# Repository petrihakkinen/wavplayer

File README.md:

# wav-player
Plays a wav file from SD card using a microcontroller

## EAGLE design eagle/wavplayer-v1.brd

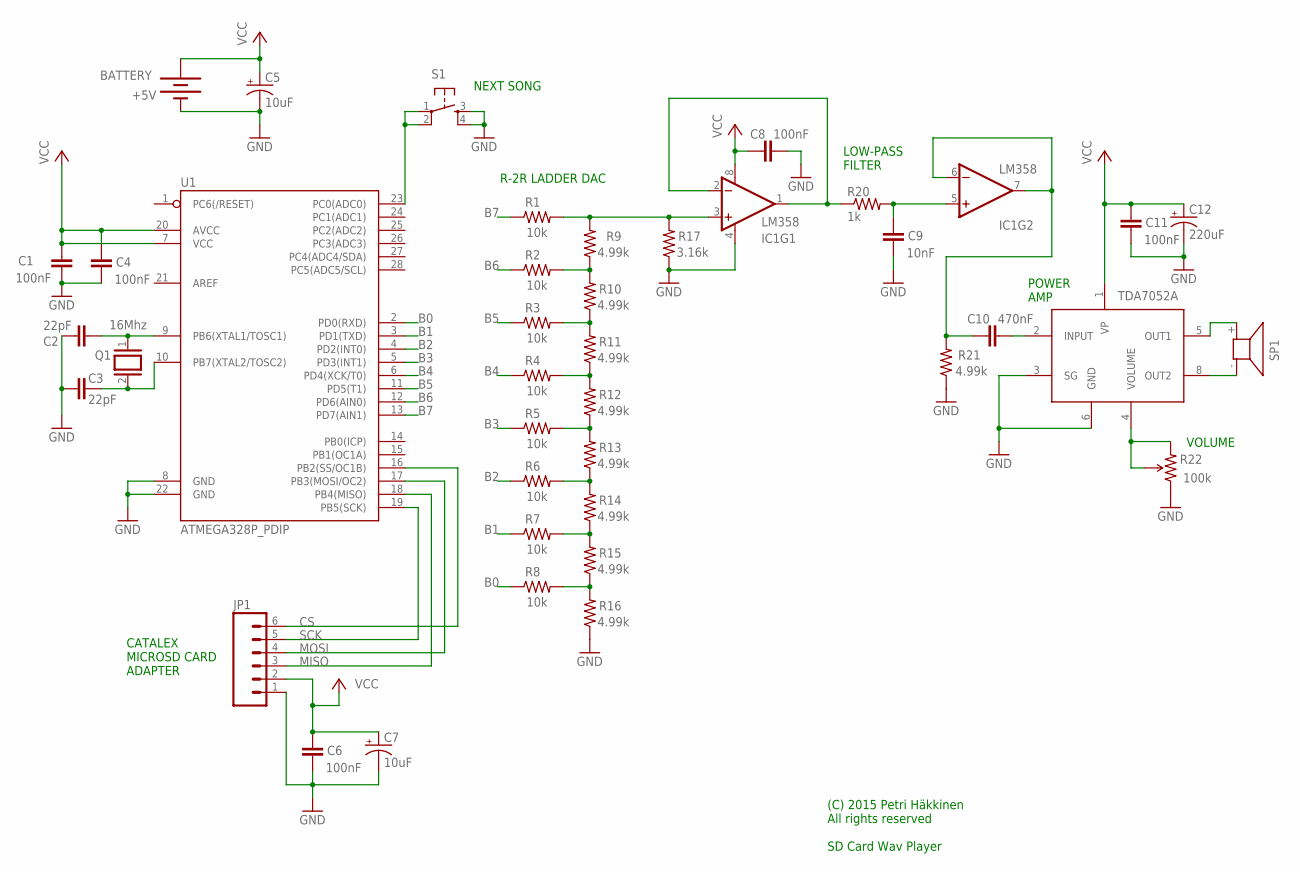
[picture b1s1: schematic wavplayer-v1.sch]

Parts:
BATTERY: +5V; BATTERY-AA
C1, C4, C6, C8, C11: 100nF; CAP-PTH-SMALL
C2, C3: 22pF; CAP-PTH-SMALL
C5, C7: 10uF; CPOL-RADIAL-100UF-25V
C9: 10nF; CAP-PTH-SMALL
C10: 470nF; CAP-PTH-SMALL
C12: 220uF; CPOL-RADIAL-100UF-25V
IC1: LM358; DIP08
JP1: M06LONGPADS; 1X06_LONGPADS
Q1: 16Mhz; QS
R1, R2, R3, R4, R5, R6, R7, R8: 10k; AXIAL-0.4
R9, R10, R11, R12, R13, R14, R15, R16, R21: 4.99k; AXIAL-0.4
R17: 3.16k; AXIAL-0.4
R20: 1k; AXIAL-0.4
R22: 100k; TRIM_POT_PTH
S1: TAC_SWITCHPTH; TACTILE-PTH
SP1: AL11P
U1: ATMEGA328P_PDIP; DIL28-3
U$1: TDA7052B; DIL08

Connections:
B0: R8.P$1 (1), U1.2 (PD0(RXD))
B1: R7.P$1 (1), U1.3 (PD1(TXD))
B2: R6.P$1 (1), U1.4 (PD2(INT0))
B3: R5.P$1 (1), U1.5 (PD3(INT1))
B4: R4.P$1 (1), U1.6 (PD4(XCK/T0))
B5: R3.P$1 (1), U1.11 (PD5(T1))
B6: R2.P$1 (1), U1.12 (PD6(AIN0))
B7: R1.P$1 (1), U1.13 (PD7(AIN1))
CS: JP1.6, U1.16 (PB2(SS/OC1B))
GND: BATTERY.GND@1 (-), C1.2, C2.2, C3.2, C4.2, C5.2 (-), C6.2, C7.2 (-), C8.2, C9.2, C11.2, C12.2 (-), IC1.4 (V-), JP1.1, R16.P$1 (1), R17.P$1 (1), R21.P$1 (1), R22.1 (CCW), S1.3, S1.4, U1.8 (GND), U1.22 (GND), U$1.3 (SG), U$1.6 (GND)
MISO: JP1.3, U1.18 (PB4(MISO))
MOSI: JP1.4, U1.17 (PB3(MOSI/OC2))
unnamed: C2.1, Q1.1, U1.9 (PB6(XTAL1/TOSC1))
unnamed: C3.1, Q1.2, U1.10 (PB7(XTAL2/TOSC2))
unnamed: R4.P$2 (2), R11.P$1 (1), R12.P$2 (2)
unnamed: R5.P$2 (2), R12.P$1 (1), R13.P$2 (2)
unnamed: R6.P$2 (2), R13.P$1 (1), R14.P$2 (2)
unnamed: R3.P$2 (2), R10.P$1 (1), R11.P$2 (2)
unnamed: R7.P$2 (2), R14.P$1 (1), R15.P$2 (2)
unnamed: R2.P$2 (2), R9.P$1 (1), R10.P$2 (2)
unnamed: R8.P$2 (2), R15.P$1 (1), R16.P$2 (2)
unnamed: IC1.3 (+IN), R1.P$2 (2), R9.P$2 (2), R17.P$2 (2)
unnamed: C9.1, IC1.5 (+IN), R20.P$2 (2)
unnamed: C10.1, IC1.6 (-IN), IC1.7 (OUT), R21.P$2 (2)
unnamed: IC1.1 (OUT), IC1.2 (-IN), R20.P$1 (1)
unnamed: SP1.- (1), U$1.8 (OUT2)
unnamed: C8.1, IC1.8 (V+)
unnamed: SP1.+ (2), U$1.5 (OUT1)
unnamed: C10.2, U$1.2 (INPUT)
unnamed: R22.2 (WIPER), R22.3 (CW), U$1.4 (VOLUME)
unnamed: S1.1, S1.2, U1.23 (PC0(ADC0))
SCK: JP1.5, U1.19 (PB5(SCK))
VCC: BATTERY.PWR@1 (+), C1.1, C4.1, C5.1 (+), C6.1, C7.1 (+), C11.1, C12.1 (+), JP1.2, U1.7 (VCC), U1.20 (AVCC), U$1.1 (VP)

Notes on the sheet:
(C) 2015 Petri Häkkinen All rights reserved SD Card Wav Player
VOLUME
TDA7052A
LOW-PASS FILTER
R-2R LADDER DAC
CATALEX MICROSD CARD ADAPTER
POWER AMP
NEXT SONG

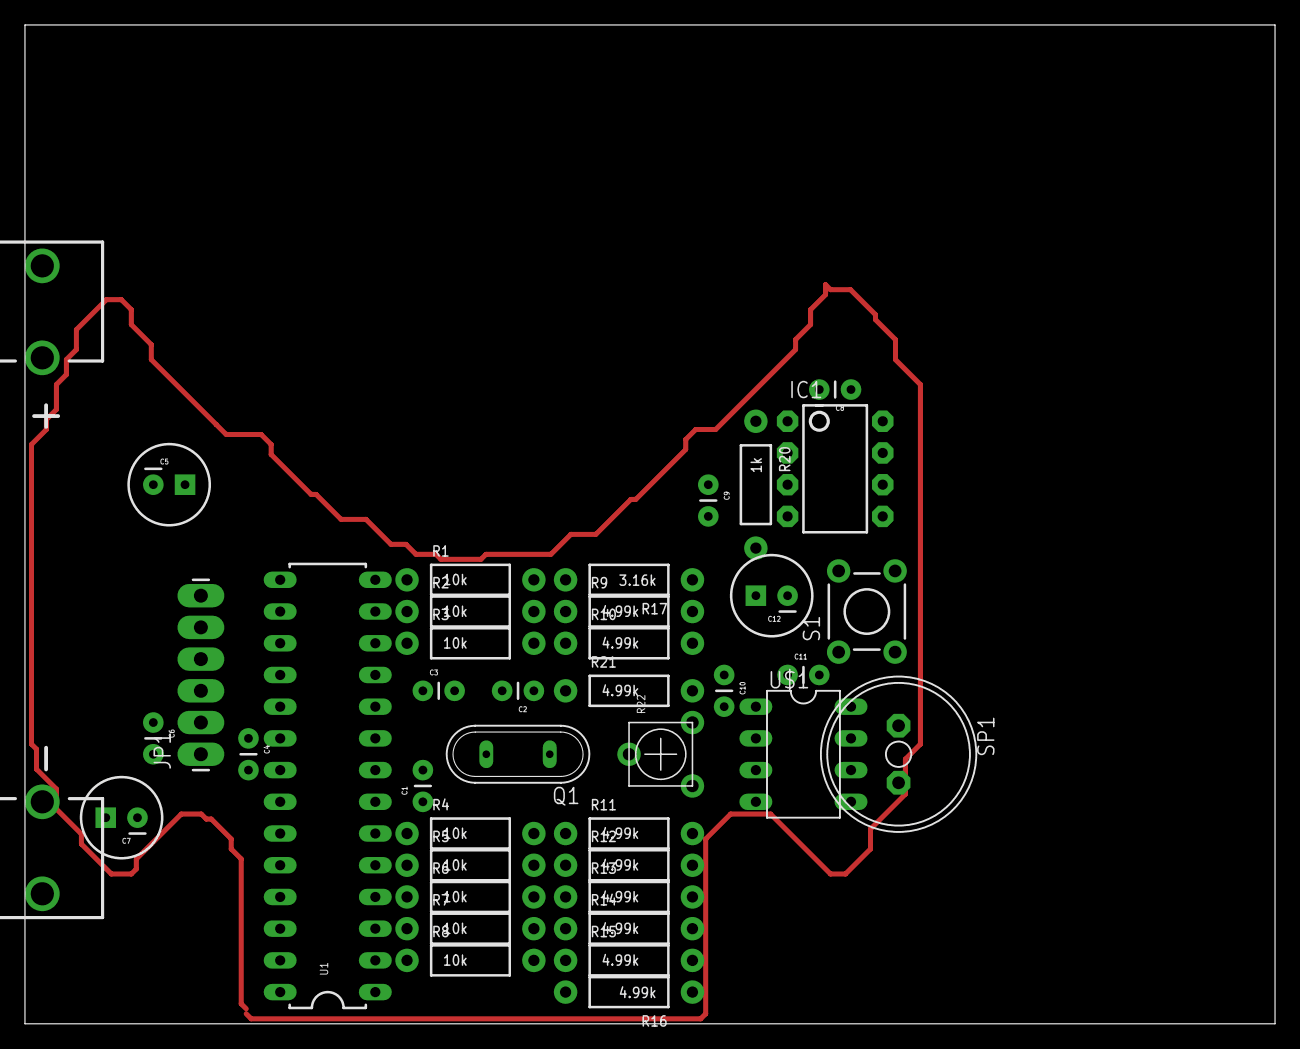
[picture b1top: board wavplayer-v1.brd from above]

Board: 2 copper layers, 100.1 x 80.0 mm, 40 parts (0 on the bottom side), 33 nets.

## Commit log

2015-09-27 SD card read test.
2015-09-27 Added sublime project.
2015-09-27 Renaming project (Arduino ide wtf!).
2015-09-27 Testing, PWM output seems to break SD card library.
2015-09-27 Shitty quality playback.
2015-09-27 Double buffering, still bad quality.
2015-10-03 31250Hz sampling rate, unsigned pcm.
2015-10-04 Started work on music converter.
2015-10-04 Resampling to 31250Hz.
2015-10-19 Multiple song support, next song button, 40000 Hz sampling rate.
2016-05-17 Added eagle files.

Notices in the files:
parts and their libraries:
SparkFun-DigitalIC: Licensing: CC v3.0 Share-Alike You are welcome to use this library for commercial purposes.
SparkFun-AnalogIC: Licensing:Creative Commons ShareAlike 4.0 International - https://creativecommons.org/licenses/by-sa/4.0
